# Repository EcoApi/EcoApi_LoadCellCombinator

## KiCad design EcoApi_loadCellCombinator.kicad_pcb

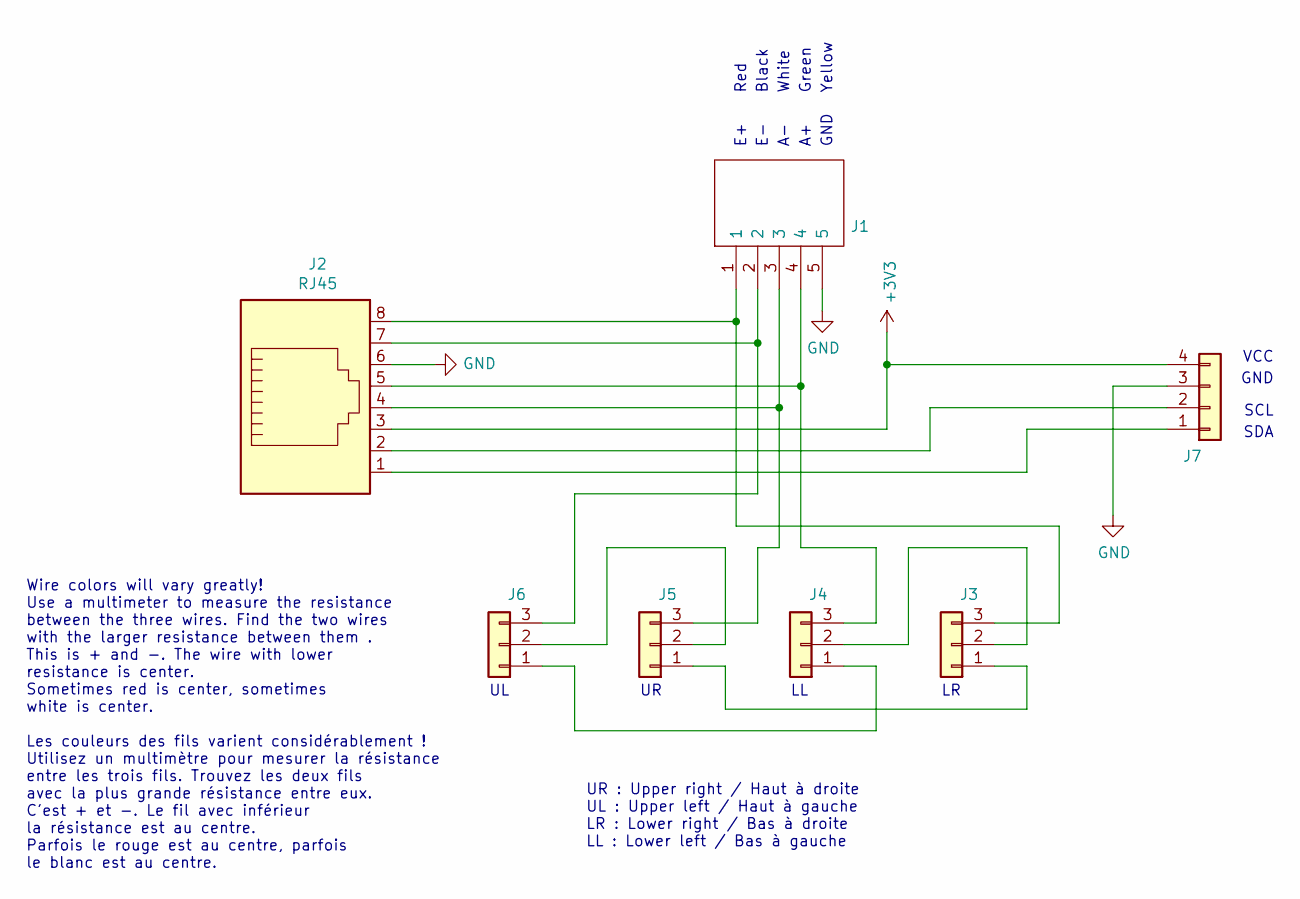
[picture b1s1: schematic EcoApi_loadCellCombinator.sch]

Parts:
J1: B5B-XH-A__LF__SN_; SHDR5W64P0X250_1X5_1490X575X700P; Manufacturer_Part_Number B5B-XH-A (LF)(SN)
J2: RJ45; 54601908WPLF
J3, J4, J5, J6: Conn_01x03; PinHeader_1x03_P2.54mm_Vertical
J7: Conn_01x04; PinHeader_1x04_P2.54mm_Vertical

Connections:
+3V3: J2.3, J7.4
GND: J1.5, J2.6, J7.3
unnamed: J1.1, J2.8, J3.3
unnamed: J1.2, J2.7, J6.3
unnamed: J1.3, J2.4, J5.3
unnamed: J1.4, J2.5, J4.3
unnamed: J2.1, J7.1
unnamed: J2.2, J7.2
unnamed: J3.1, J5.1
unnamed: J3.2, J4.2
unnamed: J4.1, J6.1
unnamed: J5.2, J6.2

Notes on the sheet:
SDA
SCL
GND
VCC
Wire colors will vary greatly! Use a multimeter to measure the resistance between the three wires. Find the two wires with the larger resistance between them . This is + and -. The wire with lower resistance is center. Sometimes red is center, sometimes white is center. Les couleurs des fils varien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
Red
Black
White
Green
Yellow
UR : Upper right / Haut à droite UL : Upper left / Haut à gauche LR : Lower right / Bas à droite LL : Lower left / Bas à gauche

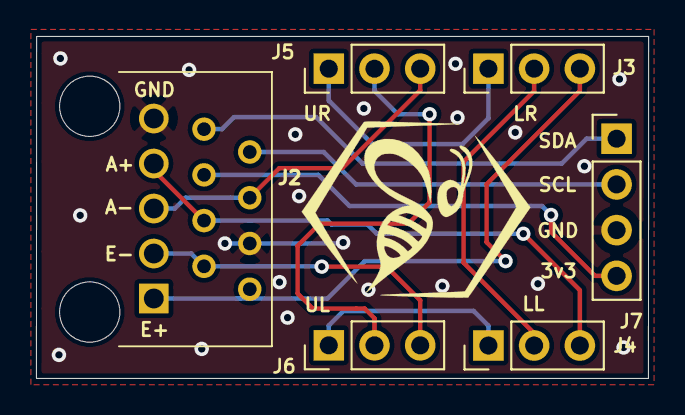
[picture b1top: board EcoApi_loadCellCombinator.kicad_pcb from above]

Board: 2 copper layers, 34.0 x 19.0 mm, 7 parts (1 on the bottom side), 12 nets.
